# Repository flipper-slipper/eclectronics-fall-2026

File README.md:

# eclectronics-fall-2026
coursework for the eclectronics class at olin collge for the fall 2026 semester. includes pcb design, project reports, circuit simulations.

## Projects
- [Miniproject 1: USB-powered 1 Hz LED flasher PCB](miniproject-1/)

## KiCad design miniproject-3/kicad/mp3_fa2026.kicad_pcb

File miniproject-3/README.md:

# Miniproject 3: RP2350 microcontroller dev board

KiCad project is in `kicad/` (open `mp3_fa2026.kicad_pro`). Assignment handout, BoM and reference schematic are in `docs/assignment/`.

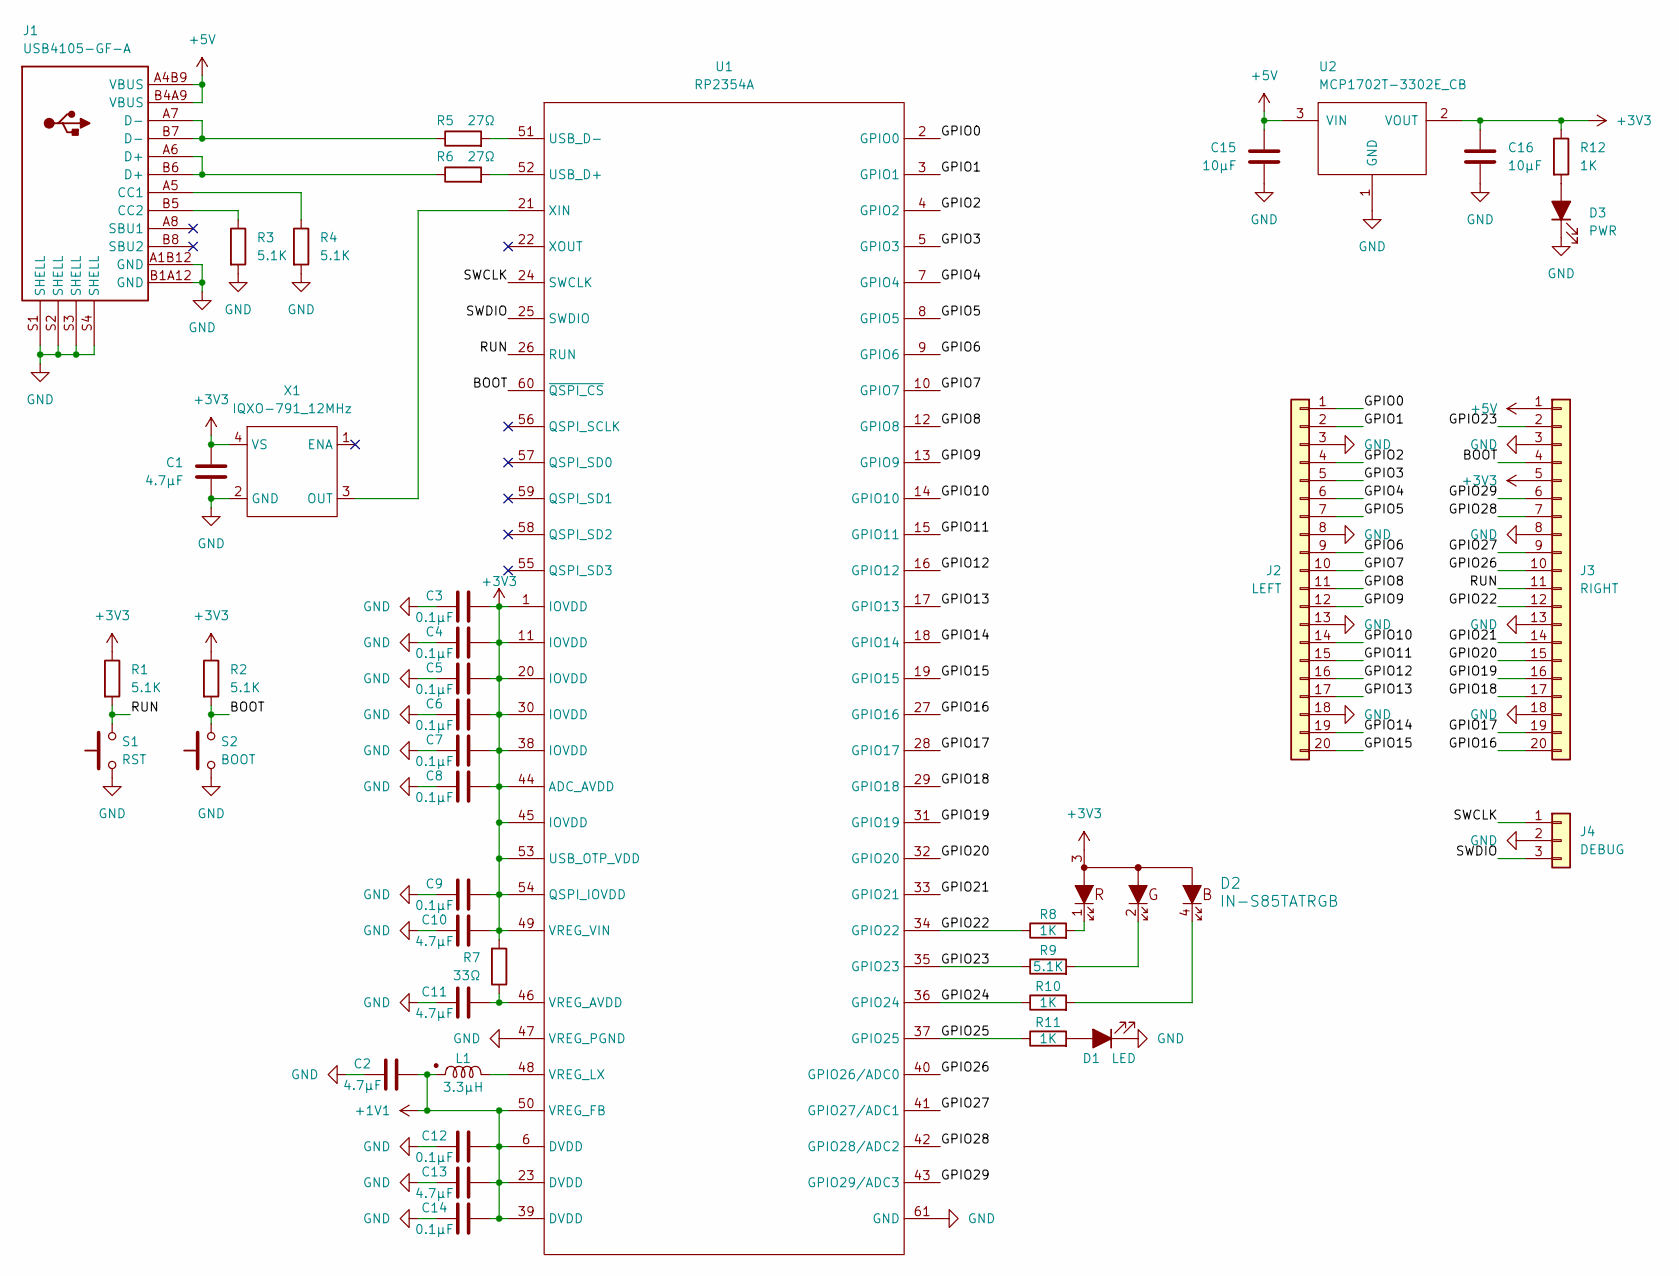
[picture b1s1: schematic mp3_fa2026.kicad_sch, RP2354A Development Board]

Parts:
C1, C2, C10: 4.7µF; C_0603_1608Metric
C3, C4, C5, C6, C7, C8, C9, C12, C14: 0.1µF; C_0402_1005Metric
C11, C13: 4.7µF; C_0402_1005Metric
C15, C16: 10µF; C_0603_1608Metric
D1: LED; LED_SunLED_XZCM2MOK54WA-1VF_0805
D2: IN-S85TATRGB; LED_Inolux_IN-S85TATRGB_2.0x1.25mm
D3: PWR; LED_LiteOn_LTST-C170_0805
J1: USB4105-GF-A; USB_C_Receptacle_GCT_USB4105-GF-A
J2: LEFT; PinHeader_1x20_P2.54mm_Vertical
J3: RIGHT; PinHeader_1x20_P2.54mm_Vertical
J4: DEBUG; PinHeader_1x03_P2.54mm_Vertical
L1: 3.3µH; L_Abracon_AOTA-B201610_2.0x1.6mm
R1, R2, R3, R4: 5.1K; R_0603_1608Metric
R5, R6: 27Ω; R_0603_1608Metric
R7: 33Ω; R_0402_1005Metric
R8, R10, R11: 1K; R_0402_1005Metric
R9: 5.1K; R_0402_1005Metric
R12: 1K; R_0603_1608Metric
S1: RST; SW_Omron_B3U-1000P
S2: BOOT; SW_Omron_B3U-1000P
U1: RP2354A; QFN-60-1EP_7x7mm_P0.4mm_EP3.4x3.4mm_RP2350A
U2: MCP1702T-3302E_CB; SOT-23_Microchip_CB
X1: IQXO-791_12MHz; Oscillator_Wurth_831056289_2.5x2.0mm

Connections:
+1V1: C2.2, C12.2, C13.2, C14.2, L1.1, U1.6 (DVDD), U1.23 (DVDD), U1.39 (DVDD), U1.50 (VREG_FB)
+3V3: C1.2, C3.2, C4.2, C5.2, C6.2, C7.2, C8.2, C9.2, C10.2, C16.1, D2.3, J3.5, R1.1, R2.1, R7.2, R12.1, U1.1 (IOVDD), U1.11 (IOVDD), U1.20 (IOVDD), U1.30 (IOVDD), U1.38 (IOVDD), U1.44 (ADC_AVDD), U1.45 (IOVDD), U1.49 (VREG_VIN), U1.53 (USB_OTP_VDD), U1.54 (QSPI_IOVDD), U2.2 (VOUT), X1.4 (VS)
+5V: C15.2, J1.A4B9 (VBUS), J1.B4A9 (VBUS), J3.1, U2.3 (VIN)
/BOOT: J3.4, R2.2, S2.2, U1.60 (~QSPI_CS)
/GPIO0: J2.1, U1.2 (GPIO0)
/GPIO1: J2.2, U1.3 (GPIO1)
/GPIO2: J2.4, U1.4 (GPIO2)
/GPIO3: J2.5, U1.5 (GPIO3)
/GPIO4: J2.6, U1.7 (GPIO4)
/GPIO5: J2.7, U1.8 (GPIO5)
/GPIO6: J2.9, U1.9 (GPIO6)
/GPIO7: J2.10, U1.10 (GPIO7)
/GPIO8: J2.11, U1.12 (GPIO8)
/GPIO9: J2.12, U1.13 (GPIO9)
/GPIO10: J2.14, U1.14 (GPIO10)
/GPIO11: J2.15, U1.15 (GPIO11)
/GPIO12: J2.16, U1.16 (GPIO12)
/GPIO13: J2.17, U1.17 (GPIO13)
/GPIO14: J2.19, U1.18 (GPIO14)
/GPIO15: J2.20, U1.19 (GPIO15)
/GPIO16: J3.20, U1.27 (GPIO16)
/GPIO17: J3.19, U1.28 (GPIO17)
/GPIO18: J3.17, U1.29 (GPIO18)
/GPIO19: J3.16, U1.31 (GPIO19)
/GPIO20: J3.15, U1.32 (GPIO20)
/GPIO21: J3.14, U1.33 (GPIO21)
/GPIO22: J3.12, R8.1, U1.34 (GPIO22)
/GPIO23: J3.2, R9.1, U1.35 (GPIO23)
/GPIO24: R10.1, U1.36 (GPIO24)
/GPIO25: R11.1, U1.37 (GPIO25)
/GPIO26: J3.10, U1.40 (GPIO26/ADC0)
/GPIO27: J3.9, U1.41 (GPIO27/ADC1)
/GPIO28: J3.7, U1.42 (GPIO28/ADC2)
/GPIO29: J3.6, U1.43 (GPIO29/ADC3)
/RUN: J3.11, R1.2, S1.2, U1.26 (RUN)
/SWCLK: J4.1, U1.24 (SWCLK)
/SWDIO: J4.3, U1.25 (SWDIO)
GND: C1.1, C2.1, C3.1, C4.1, C5.1, C6.1, C7.1, C8.1, C9.1, C10.1, C11.1, C12.1, C13.1, C14.1, C15.1, C16.2, D1.1 (K), D3.1 (K), J1.A1B12 (GND), J1.B1A12 (GND), J1.S1 (SHELL_S1), J1.S2 (SHELL_S1), J1.S3 (SHELL_S1), J1.S4 (SHELL_S1), J2.3, J2.8, J2.13, J2.18, J3.3, J3.8, J3.13, J3.18, J4.2, R3.2, R4.2, S1.1, S2.1, U1.47 (VREG_PGND), U1.61 (GND), U2.1 (GND), X1.2 (GND)
unnamed: D1.2 (A), R11.2
unnamed: D2.1, R8.2
unnamed: D2.2, R9.2
unnamed: D2.4, R10.2
unnamed: D3.2 (A), R12.2
unnamed: J1.A5 (CC1_A5), R4.1
unnamed: J1.B5 (CC2_B5), R3.1
unnamed: J1.A6 (D+_A6), J1.B6 (D+_B6), R6.1
unnamed: J1.A7 (D-_A7), J1.B7 (D-_B7), R5.1
unnamed: R6.2, U1.52 (USB_D+)
unnamed: R5.2, U1.51 (USB_D-)
unnamed: C11.2, R7.1, U1.46 (VREG_AVDD)
unnamed: L1.2, U1.48 (VREG_LX)
unnamed: U1.21 (XIN), X1.3 (OUT)

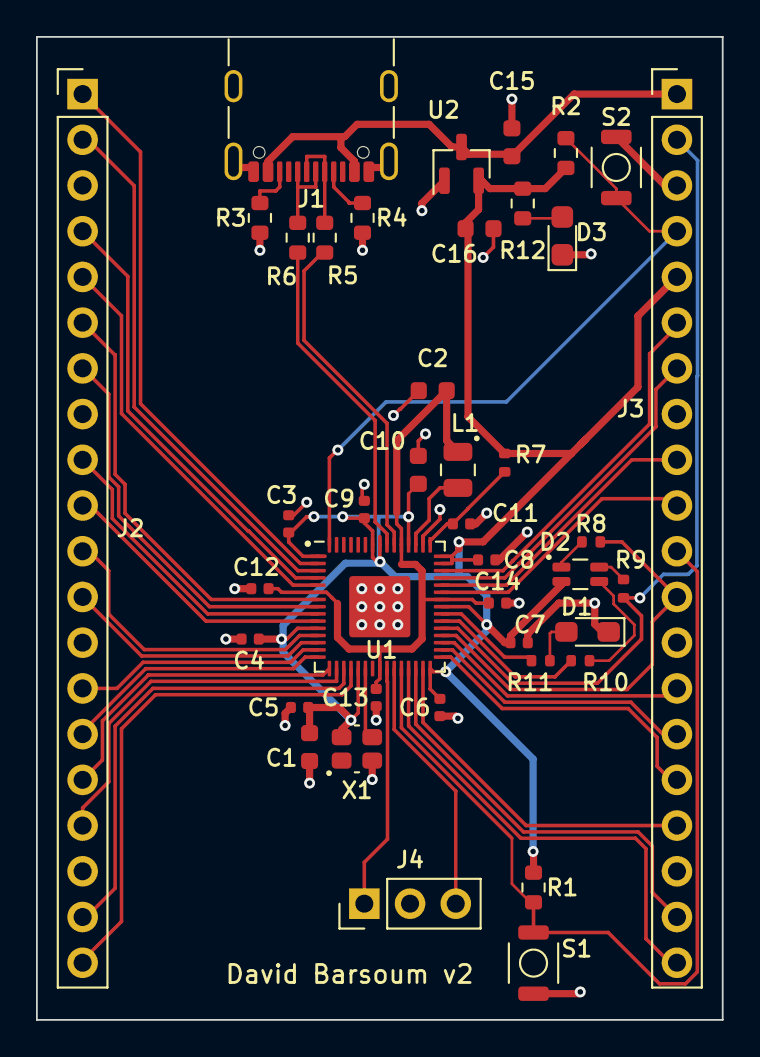
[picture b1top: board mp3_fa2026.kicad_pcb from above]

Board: 2 copper layers, 38.1 x 54.6 mm, 41 parts (0 on the bottom side), 52 nets.

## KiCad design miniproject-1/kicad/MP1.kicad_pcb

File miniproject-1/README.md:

# Miniproject 1: USB-powered 1 Hz LED flasher

Read the report to learn more.

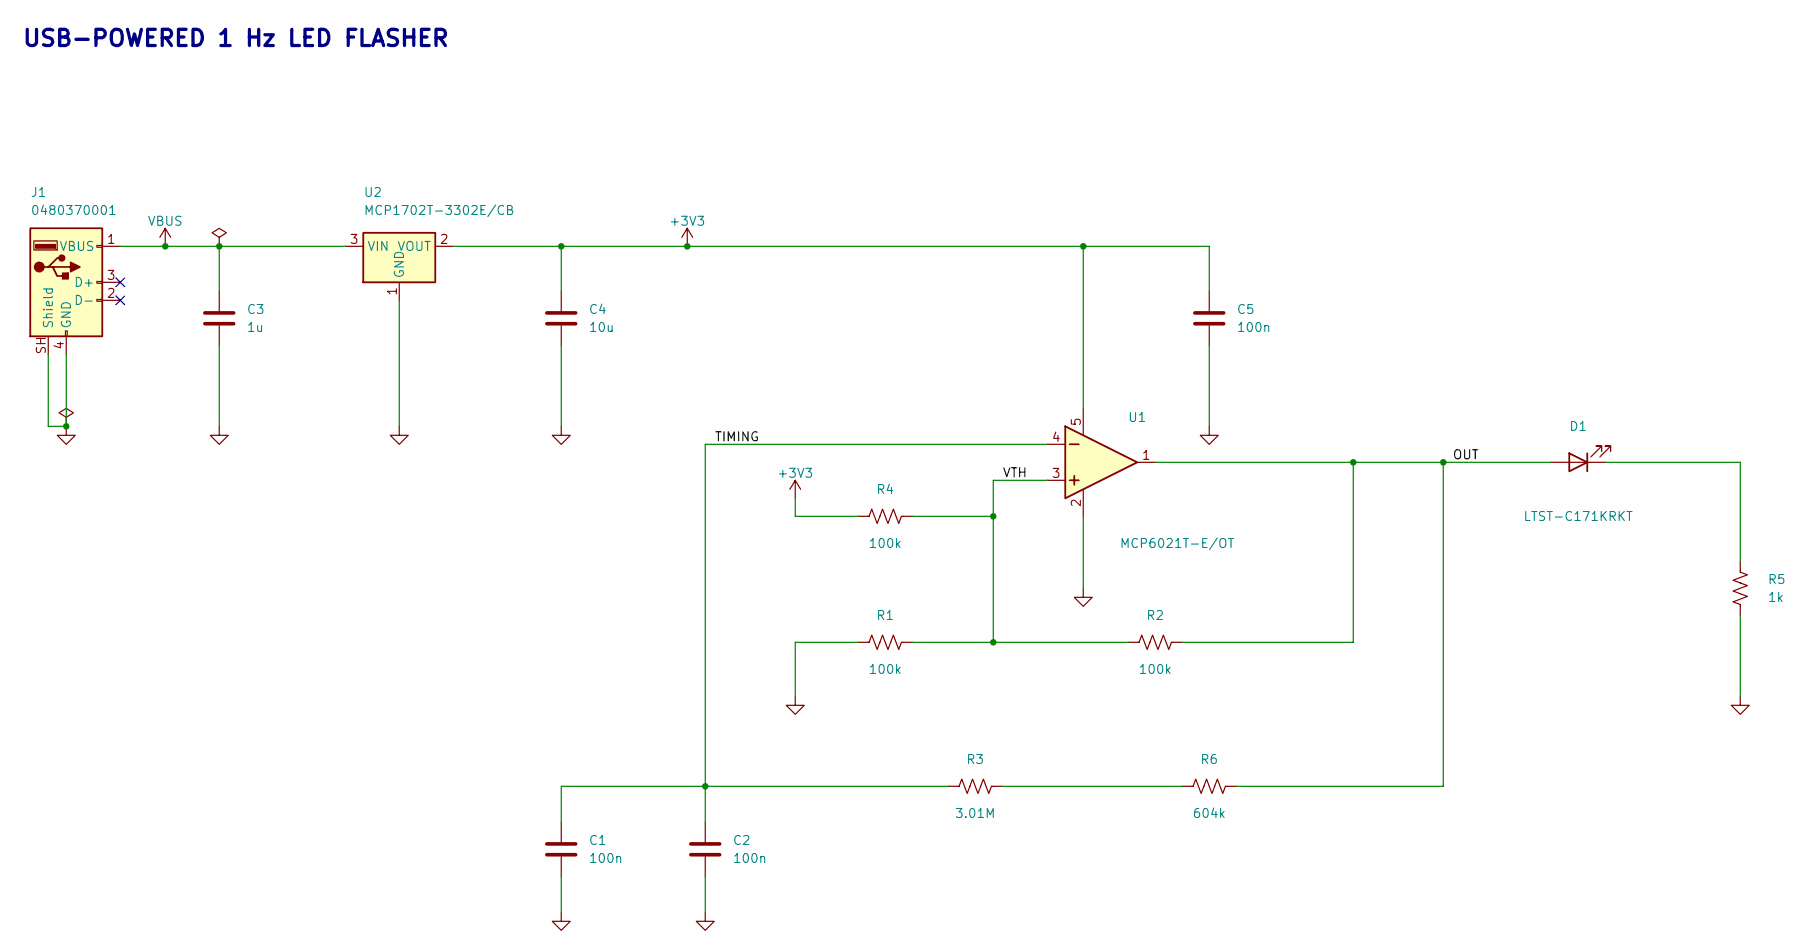
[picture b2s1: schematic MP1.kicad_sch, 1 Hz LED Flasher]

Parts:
C1, C2, C5: 100n; C_0603_1608Metric; Voltage 50 V; Tolerance 5%; MPN CC0603JRX7R9BB104; DigiKey 311-1779-1-ND
C3: 1u; C_0603_1608Metric; Voltage 25 V; Tolerance 10%; MPN C0603C105K3RACTU; DigiKey 399-7376-1-ND
C4: 10u; C_0603_1608Metric; Voltage 16 V; Tolerance 10%; MPN GRT188R61C106KE13D; DigiKey 490-12317-1-ND
D1: LTST-C171KRKT; LED_0805_2012Metric; MPN LTST-C171KRKT; DigiKey 160-1427-1-ND
J1: 0480370001; USB_A_Molex_48037-0001_Horizontal; MPN 0480370001; DigiKey WM17117-ND
R1, R2, R4: 100k; R_0603_1608Metric; Tolerance 1%; MPN RC0603FR-07100KL; DigiKey 311-100KHRCT-ND
R3: 3.01M; R_0603_1608Metric; Tolerance 1%; MPN RC0603FR-073M01L; DigiKey 311-3.01MHRCT-ND
R5: 1k; R_0603_1608Metric; Tolerance 1%; MPN RC0603FR-071KL; DigiKey 311-1.00KHRCT-ND
R6: 604k; R_0603_1608Metric; Tolerance 1%; MPN RC0603FR-07604KL; DigiKey 311-604KHRCT-ND
U1: MCP6021T-E/OT; SOT-23-5; MPN MCP6021T-E/OT; DigiKey MCP6021T-E/OTCT-ND
U2: MCP1702T-3302E/CB; SOT-23; MPN MCP1702T-3302E/CB; DigiKey MCP1702T-3302E/CBCT-ND

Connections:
+3V3: C4.1, C5.1, R4.1, U1.5 (VDD), U2.2 (VOUT)
/OUT: D1.2 (A), R2.2, R6.2, U1.1
/TIMING: C1.1, C2.1, R3.1, U1.4 (-)
/VTH: R1.2, R2.1, R4.2, U1.3 (+)
GND: C1.2, C2.2, C3.2, C4.2, C5.2, J1.4 (GND), J1.SH (Shield), R1.1, R5.2, U1.2 (VSS), U2.1 (GND)
unnamed: D1.1 (K), R5.1
unnamed: R3.2, R6.1
VBUS: C3.1, J1.1 (VBUS), U2.3 (VIN)

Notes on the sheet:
USB-POWERED 1 Hz LED FLASHER

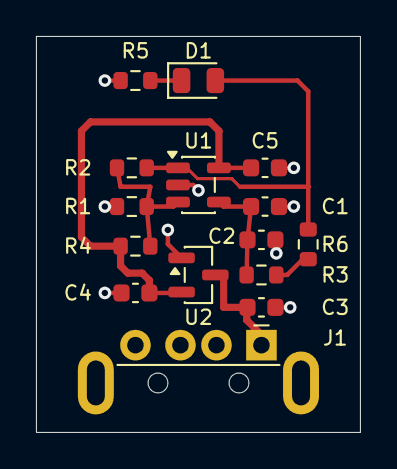
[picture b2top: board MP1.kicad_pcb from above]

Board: 2 copper layers, 18.0 x 22.0 mm, 15 parts (0 on the bottom side), 8 nets.
